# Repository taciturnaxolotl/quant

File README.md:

<h3 align="center">
    <br/>
    
    <span>Quant</span>
    
</h3>

<p align="center">
    <i>noun - An expert in the use of mathematics and related subjects, particularly in investment management and stock trading.</i>
</p>

## What's this?

This is the repo for my macropad! It was made for the [hackpad](https://hackpad.hackclub.com/) ysws! It uses a `XIAO-RP2040-DIP` as the mcu and is currently very wip.

> [!WARNING]
> This is a work in progress and is not yet ready for use. listen to the warning 💀 🏴‍☠️

### Keymap

| | Col 1 | Col 2 | Col 3 |
| --- | --- | --- | --- |
| **Row 1** | Previous Media | Play/Pause Media | Next Media |
| **Row 2** | Mute | Volume Down | Volume Up |
| **Row 3** | Print Screen | Ctrl + Print Screen (Print Window) | Ctrl + Alt + Period (Open Emoji Keyboard) |

### BOM

| Part | Quantity | Description |
| --- | --- | --- |
| `XIAO-RP2040-DIP` | 1 | The microcontroller |
| `Kailh Choc V2` | 9 | The switches |
| `Kailh Choc V2 Keycaps` | 9 | The keycaps |
| `SK6812 MINI-E LEDs` | 6 | The pretty blinken lights |

## Fancy Screenshots

Fresh off the buffer here are some screenshots of the pcb, schematic, and case!

### PCB

### Schematic

### Case

The case can be found at [this link](https://cad.onshape.com/documents/915d8a08680b6a58046d785c/w/3a505c41cf8d6fe4a9ae9373/e/5f5e5603c47ed25f33acaea0?renderMode=0&uiState=67aef3f3f5640914345c0fd7) in onshape!

## Why that License?

Well I like using the AGPL 3.0 license because it's a strong copyleft license that ensures that any changes made to the code are shared back with the community. However there is often alot of confusion about how the license works. Here are 3 brief cases showing how the AGPL 3.0 license works:

1. You download the binary from the releases or use a hosted version.
    - You haven't done anything to the code so you are entirely in the clear!
2. You see a problem with the code so you fork it and use it privately
    - You are still in the clear! The AGPL 3.0 license only requires you to share the code if you distribute it.
3. You find an improvement, implement it, and distribute it privately in your company or for some family and friends
    - You are still in the clear! The AGPL 3.0 license only requires you to share the code if you distribute it to the public.

Basically if you distribute the code publicaly you have to share the code, but if you don't distribute the code publicaly or don't modify it then you don't have to share the code.

<p align="center">
	<code>&copy 2025-present <a href="https://github.com/taciturnaxolotl">Kieran Klukas</a></code>
</p>

<p align="center">
	
</p>

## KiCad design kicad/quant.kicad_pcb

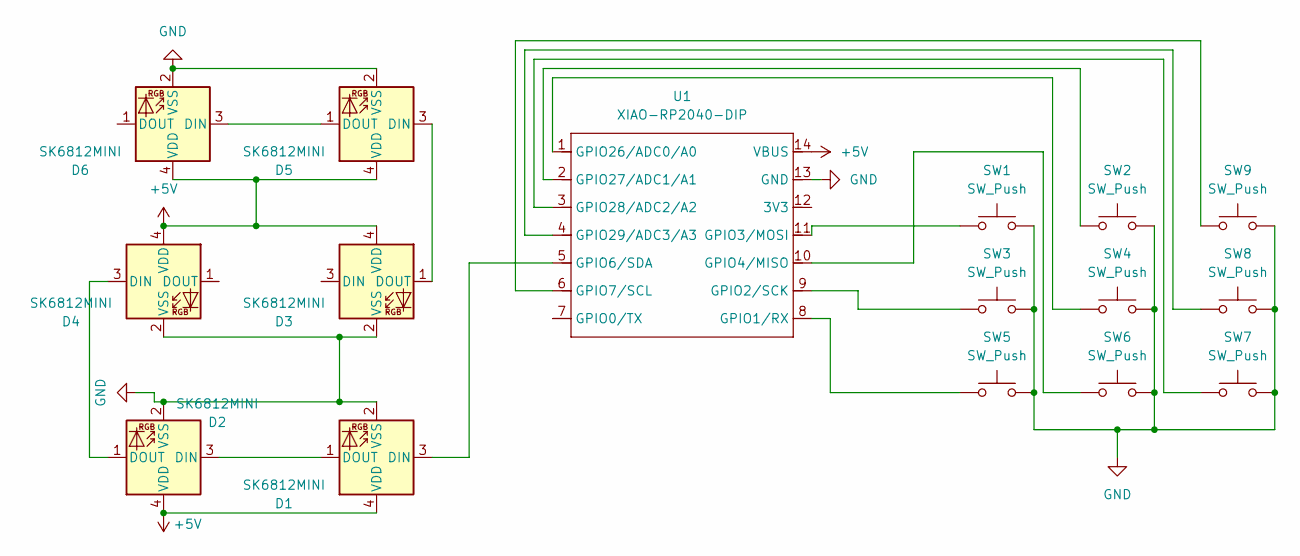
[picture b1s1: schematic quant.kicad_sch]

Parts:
D1, D2, D3, D4, D5, D6: SK6812MINI; LED_SK6812MINI_PLCC4_3.5x3.5mm_P1.75mm
SW1, SW2, SW3, SW4, SW5, SW6, SW7, SW8, SW9: SW_Push; Kailh-PG1353-Solderable-1U
U1: XIAO-RP2040-DIP

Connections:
+5V: D1.4 (VDD), D2.4 (VDD), D3.4 (VDD), D4.4 (VDD), D5.4 (VDD), D6.4 (VDD), U1.14 (VBUS)
GND: D1.2 (VSS), D2.2 (VSS), D3.2 (VSS), D4.2 (VSS), D5.2 (VSS), D6.2 (VSS), SW1.2, SW2.2, SW3.2, SW4.2, SW5.2, SW6.2, SW7.2, SW8.2, SW9.2, U1.13 (GND)
unnamed: D1.3 (DIN), U1.5 (GPIO6/SDA)
unnamed: D1.1 (DOUT), D2.3 (DIN)
unnamed: D2.1 (DOUT), D4.3 (DIN)
unnamed: D3.1 (DOUT), D5.3 (DIN)
unnamed: D5.1 (DOUT), D6.3 (DIN)
unnamed: SW5.1, U1.8 (GPIO1/RX)
unnamed: SW3.1, U1.9 (GPIO2/SCK)
unnamed: SW1.1, U1.11 (GPIO3/MOSI)
unnamed: SW6.1, U1.10 (GPIO4/MISO)
unnamed: SW9.1, U1.6 (GPIO7/SCL)
unnamed: SW4.1, U1.1 (GPIO26/ADC0/A0)
unnamed: SW2.1, U1.2 (GPIO27/ADC1/A1)
unnamed: SW7.1, U1.3 (GPIO28/ADC2/A2)
unnamed: SW8.1, U1.4 (GPIO29/ADC3/A3)

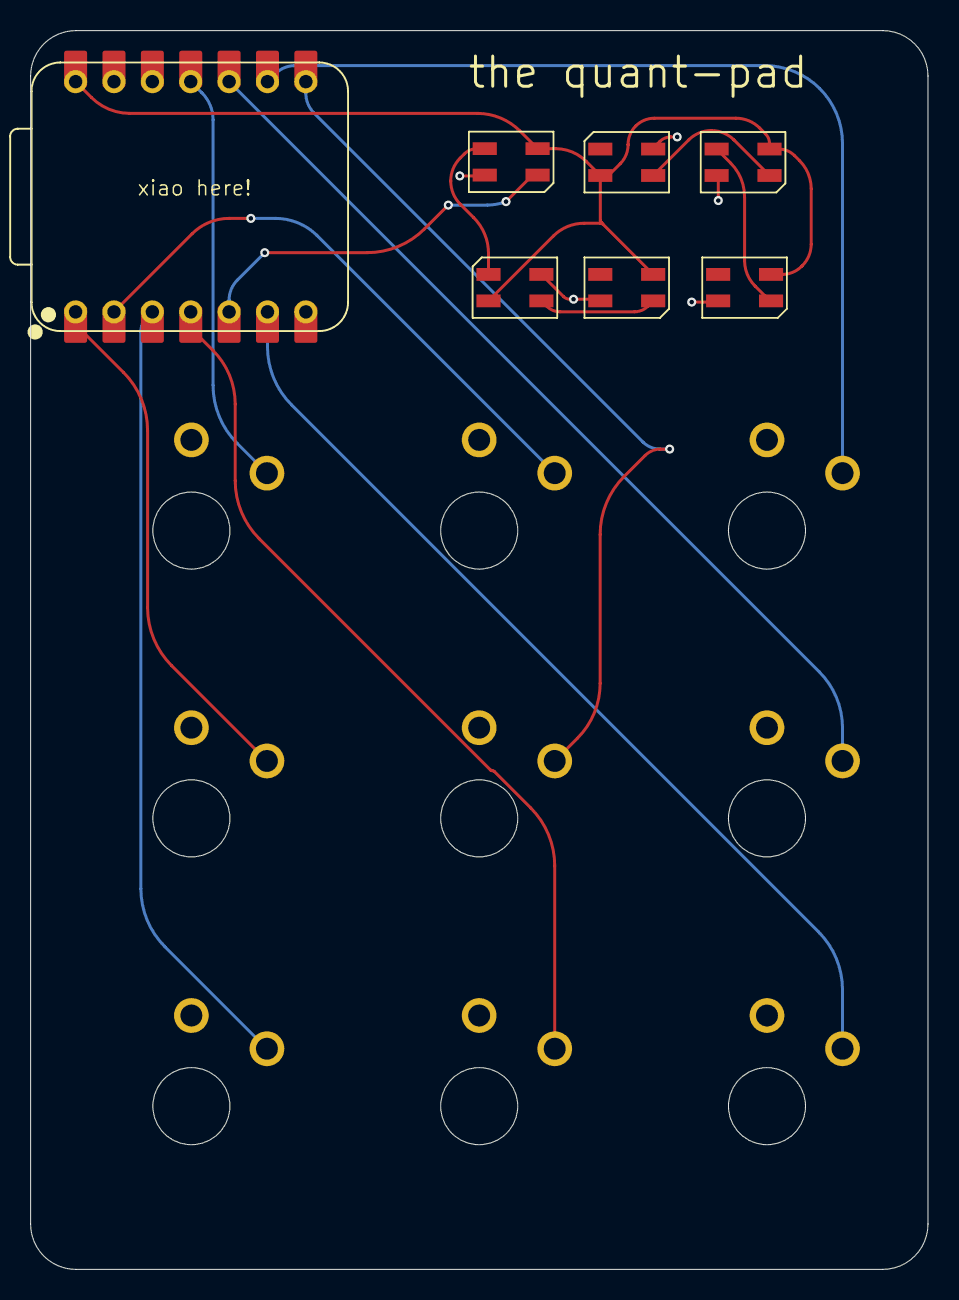
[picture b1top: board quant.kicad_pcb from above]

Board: 2 copper layers, 59.4 x 82.0 mm, 16 parts (0 on the bottom side), 16 nets.

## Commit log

2025-02-14 docs: customize
2025-02-14 feat: add pcb
2025-02-14 docs: formating
2025-02-14 docs: align images
2025-02-14 chore: remove redundant img
2025-02-14 feat: add cad
2025-02-14 docs: change image size
2025-02-14 feat: add firmware
2025-02-14 chore: change text to the quant-pad
2025-02-14 docs: add keymap
2025-02-14 docs: add bom
2025-02-14 feat: add led support
2025-02-14 docs: switch out logo
2025-02-14 docs: relicense under mit
2025-02-14 chore: move libraries to local repo
2025-02-14 feat: add prod
2025-02-14 chore: fix drc
2025-02-14 chore: move vias off pads
2025-02-14 docs: update ss
2025-02-15 feat: update cad to have a full assembly
2025-02-17 feat: add WAPWAPWAP text to silk screen back
2025-03-05 chore: kicad 9

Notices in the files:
README.md:
https://img.shields.io/static/v1.svg?style=for-the-badge&label=License&message=AGPL
